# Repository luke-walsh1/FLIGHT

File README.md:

## FLIGHT

FLIGHT is a custom, high-performance rocket flight computer designed around a Raspberry Pi Pico (RP2040) to track, log, and deploy parachutes using a servo.

## Disclaimer
### The provided code is tested and working with the hardware; however, the servo and arm button controls can be customized to suit your specific needs and are not implimented in the code:)

---

---

## Features

* Core Processing: Raspberry Pi Pico running custom data-logging, and control scripts.

* Integrated Sensors (GY-91): Combines an IMU (accelerometer/gyroscope) to measure high-G launch forces (± 16g) and orientation, alongside a precision barometer (BMP280) to calculate real-time altitude changes.

* Recovery: Dedicated PWM outputs to trigger a servo mechanism for physical parachute deployment at apogee or however you wish to use it. not implimented in code, challange for yourself :)

* Power & Protection Circuitry: Integrated TP4056 LiPo charging network backed by a comprehensive safety protection block (DW01A controller + FS8205A dual-MOSFET switch) to safely manage battery current and prevent over-discharge.

* Voltage Regulation (MT3608): A  DC-DC boost converter circuit to cleanly step up battery power to a stable $5\text{V}$ line for the onboard servo control.

---

## Mechanical & Layout Design

* Developed on a dual-layer PCB with a massive Ground Plane optimized for low electrical noise and high signal integrity.
  
* Designed with wide, heavy-current traces ($0.8\text{mm} - 1.0\text{mm}$) on the critical power highway loops (+BATT and -BATT) to safely absorb massive amp spikes when the deployment servos actuate.
  
* Custom aerospace graphics and visual infographics directly on the silkscreen layer.

# DATA

The goal is to log data. FLIGHT saves data in a format that looks like this:

---

These numbers by themselves arent that helpfull however with the help of a python program we can graph this data and mark the max altitude and other data points.

---

---

Included in the files is also a 3d printable bracket to mount flight to your rocket,
step file for your own needs.
M3 countersunk screw holes for mounting to rocket.

More on my YouTube and Stardance Profile:

https://stardance.hackclub.com/projects/18720

https://www.youtube.com/watch?v=rl3e3K6eBTs

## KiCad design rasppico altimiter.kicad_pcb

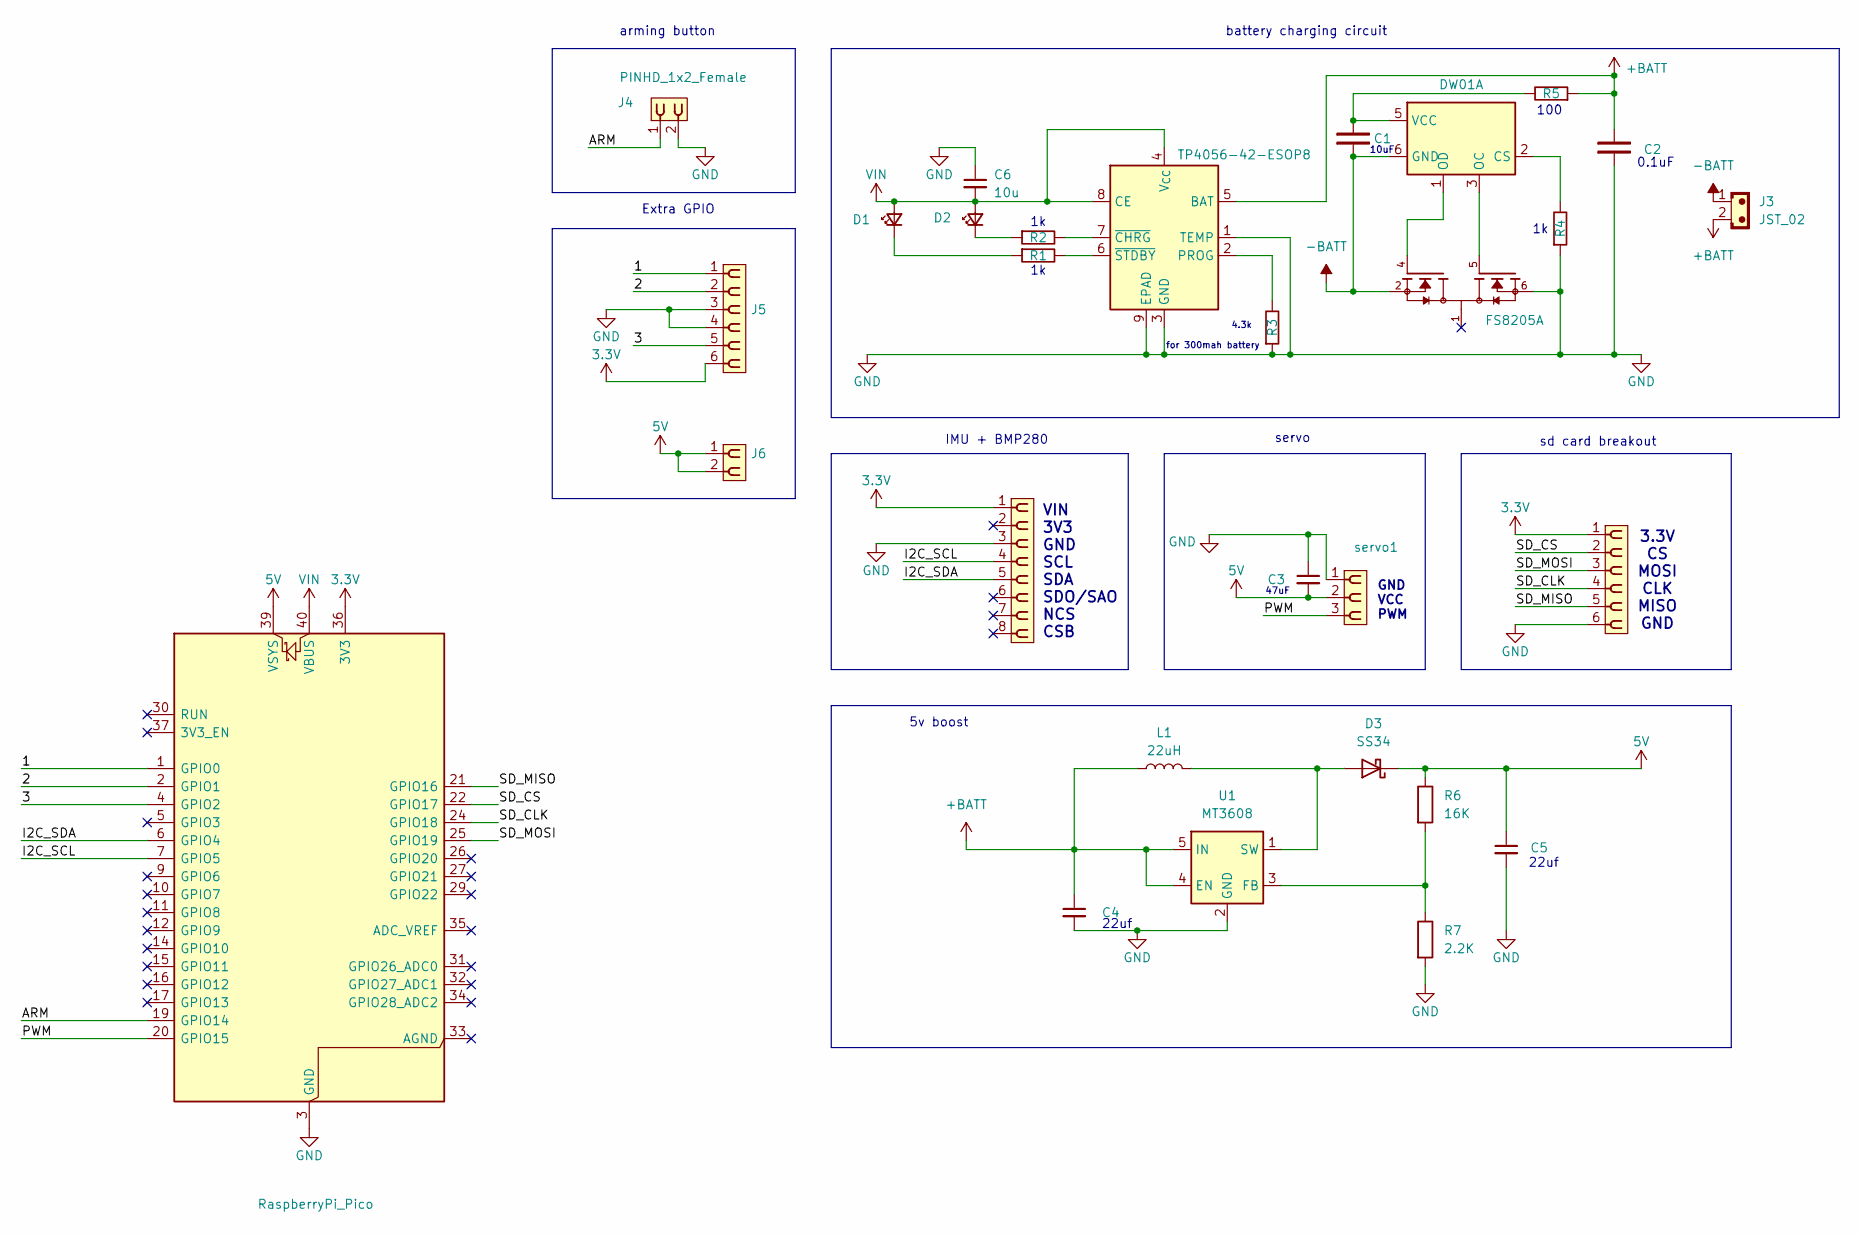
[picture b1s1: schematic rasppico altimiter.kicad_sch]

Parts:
A2: RaspberryPi_Pico; RaspberryPi_Pico_Common_Unspecified
C1, C2: Capacitor_NP; C_0805_2012Metric
C3, C4, C5: C; C_0805_2012Metric; Voltage 1kV; Tolerance 100%
C6: 10u; C_0603_1608Metric; Voltage 1kV; Tolerance 100%
D1, D2: LED; LED_0805_2012Metric
D3: SS34; D_SMA
J1, J5: PINHD_1x6_Female; PinSocket_1x06_P2.54mm_Vertical
J2: PINHD_1x8_Female; PinSocket_1x08_P2.54mm_Vertical
J3: JST_02; JST_PH_S2B-PH-K_1x02_P2.00mm_Horizontal
J4, J6: PINHD_1x2_Female; PinSocket_1x02_P2.54mm_Vertical
L1: 22uH; L_10.4x10.4_H4.8
Q1: FS8205A; SOP65P640X120-8N; PARTREV 1.7
R1, R2, R3, R4, R5: Resistor; R_0805_2012Metric
R6: 16K; R_0805_2012Metric
R7: 2.2K; R_0805_2012Metric
U1: MT3608; SOT-23-6
U4: TP4056-42-ESOP8; SOIC-8-1EP_3.9x4.9mm_P1.27mm_EP2.41x3.3mm_ThermalVias
U5: DW01A; SOT-23-6
servo1: PINHD_1x3_Female; PinSocket_1x03_P2.54mm_Vertical

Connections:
3.3V: A2.36 (3V3), J1.1, J2.1, J5.6
5V: A2.39 (VSYS), C3.2, C5.1, D3.1 (K), J6.1, J6.2, R6.1, servo1.2
+BATT: C2.2, C4.1, J3.2, L1.1, R5.1, U1.4 (EN), U1.5 (IN), U4.5 (BAT)
-BATT: C1.1, J3.1, Q1.2, Q1.3, U5.6 (GND)
/1: A2.1 (GPIO0), J5.1
/2: A2.2 (GPIO1), J5.2
/3: A2.4 (GPIO2), J5.5
/ARM: A2.19 (GPIO14), J4.1
/I2C_SCL: A2.7 (GPIO5), J2.4
/I2C_SDA: A2.6 (GPIO4), J2.5
/PWM: A2.20 (GPIO15), servo1.3
/SD_CLK: A2.24 (GPIO18), J1.4
/SD_CS: A2.22 (GPIO17), J1.2
/SD_MISO: A2.21 (GPIO16), J1.5
/SD_MOSI: A2.25 (GPIO19), J1.3
GND: A2.3 (GND), A2.8 (GND), A2.13 (GND), A2.18 (GND), A2.23 (GND), A2.28 (GND), A2.38 (GND), C2.1, C3.1, C4.2, C5.2, C6.1, J1.6, J2.3, J4.2, J5.3, J5.4, Q1.6, Q1.7, R3.1, R4.1, R7.2, U1.2 (GND), U4.1 (TEMP), U4.3 (GND), U4.9 (EPAD), servo1.1
unnamed: D1.1 (K), R1.1
unnamed: D2.1 (K), R2.1
unnamed: D3.2 (A), L1.2, U1.1 (SW)
unnamed: R6.2, R7.1, U1.3 (FB)
unnamed: R3.2, U4.2 (PROG)
unnamed: R2.2, U4.7 (~CHRG)
unnamed: R1.2, U4.6 (~STDBY)
unnamed: R4.2, U5.2 (CS)
unnamed: Q1.5, U5.3 (OC)
unnamed: Q1.4, U5.1 (OD)
unnamed: C1.2, R5.2, U5.5 (VCC)
VIN: A2.40 (VBUS), C6.2, D1.2 (A), D2.2 (A), U4.4 (V_{CC}), U4.8 (CE)

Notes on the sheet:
GND VCC PWM
Extra GPIO
22uf
100
battery charging circuit
VIN 3V3 GND SCL SDA SDO/SAO NCS CSB
sd card breakout
47uF
4.3k for 300mah battery
servo
0.1uF
5v boost
10uF
3.3V CS MOSI CLK MISO GND
IMU + BMP280
arming button

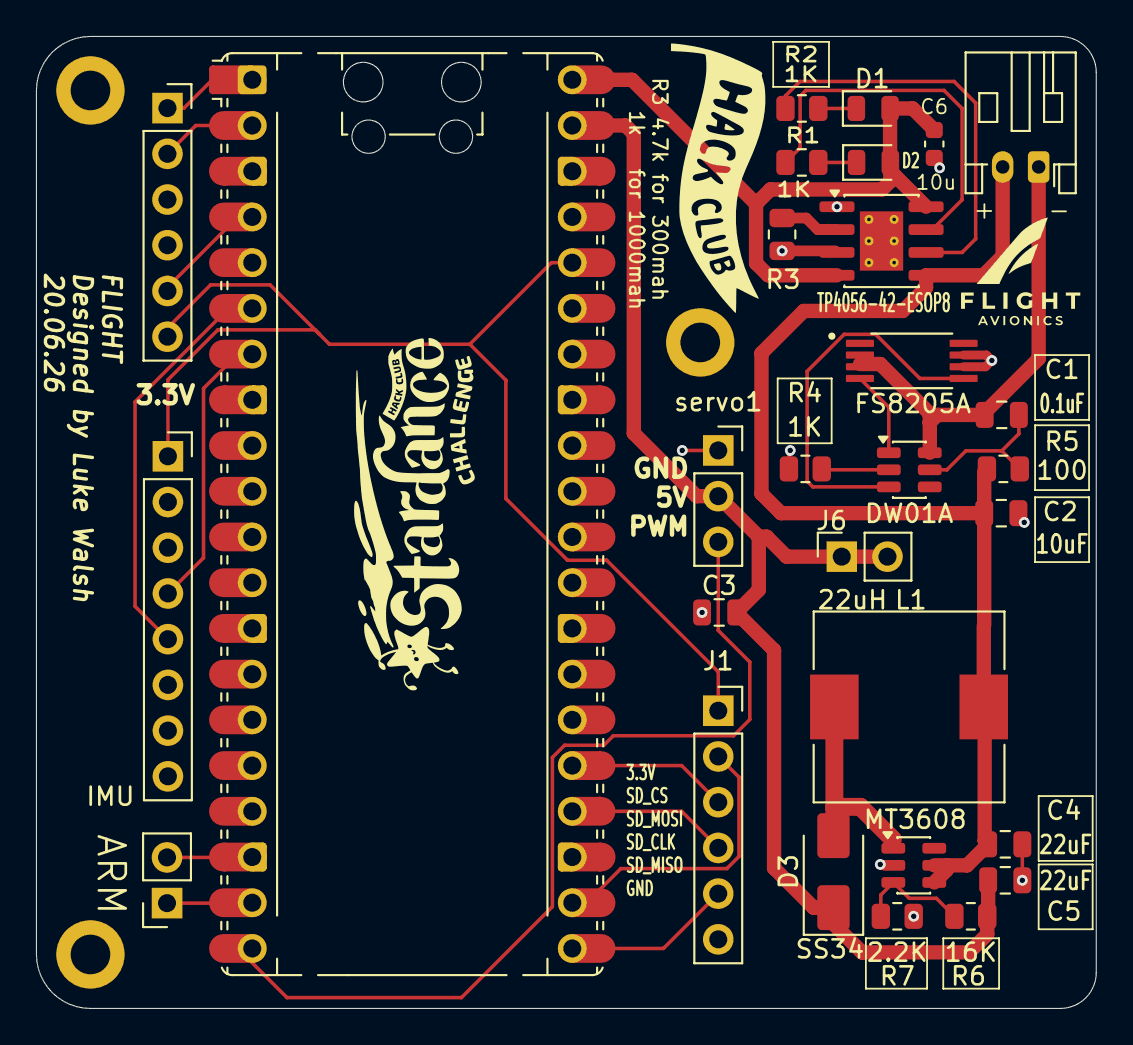
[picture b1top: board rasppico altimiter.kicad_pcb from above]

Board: 2 copper layers, 58.9 x 54.0 mm, 29 parts (0 on the bottom side), 28 nets.

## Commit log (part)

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2026-06-20 Fix typo in README description
2026-06-20 Enhance README with detailed project specifications
    Expanded the README to include details about core processing, integrated sensors, actuation, power circuitry, and voltage regulation.
2026-06-20 Enhance README with features and design details
    Added detailed features and mechanical design sections to the README.
2026-06-22 Enhance README with images and formatting updates
    Added images and improved formatting in the README.
2026-06-22 Update README to mark project as WIP
    Added a note indicating the project is a work in progress.
2026-06-22 Improve WIP note formatting in README
    Updated WIP project note formatting in README.
2026-06-23 Fix formatting of project status in README
2026-06-24 Revise README with updated title and description
    Updated project title and improved description formatting.
2026-06-24 Add image to README for visual reference
2026-06-24 Add flight core system code in FLIGHT_CODE.md
    This file contains the code for the flight core system, including hardware pin configuration, initialization, and active flight runtime logging.
2026-06-25 Revise README with updated images and feature notes
    Updated images and descriptions for clarity and accuracy. Added notes on implementation status for features.
2026-06-25 Add Bill of Materials (BOM) for project components
2026-06-25 Document data logging format and usage
    Added data logging format and example to README.
2026-06-25 Replace flight image with a larger version
    Updated the image in the README to a larger size.
2026-06-25 Add flight data analysis script with visualizations
2026-06-25 Rename FINAL V1.7.rar to GERBER FILES V1.7.rar
2026-06-25 Include additional resource links in README
    Added links to YouTube and Stardance profile for more information.
2026-06-29 Clarify recovery mechanism description in README
    Updated the description for the actuation/recovery section to clarify the functionality and challenge.
